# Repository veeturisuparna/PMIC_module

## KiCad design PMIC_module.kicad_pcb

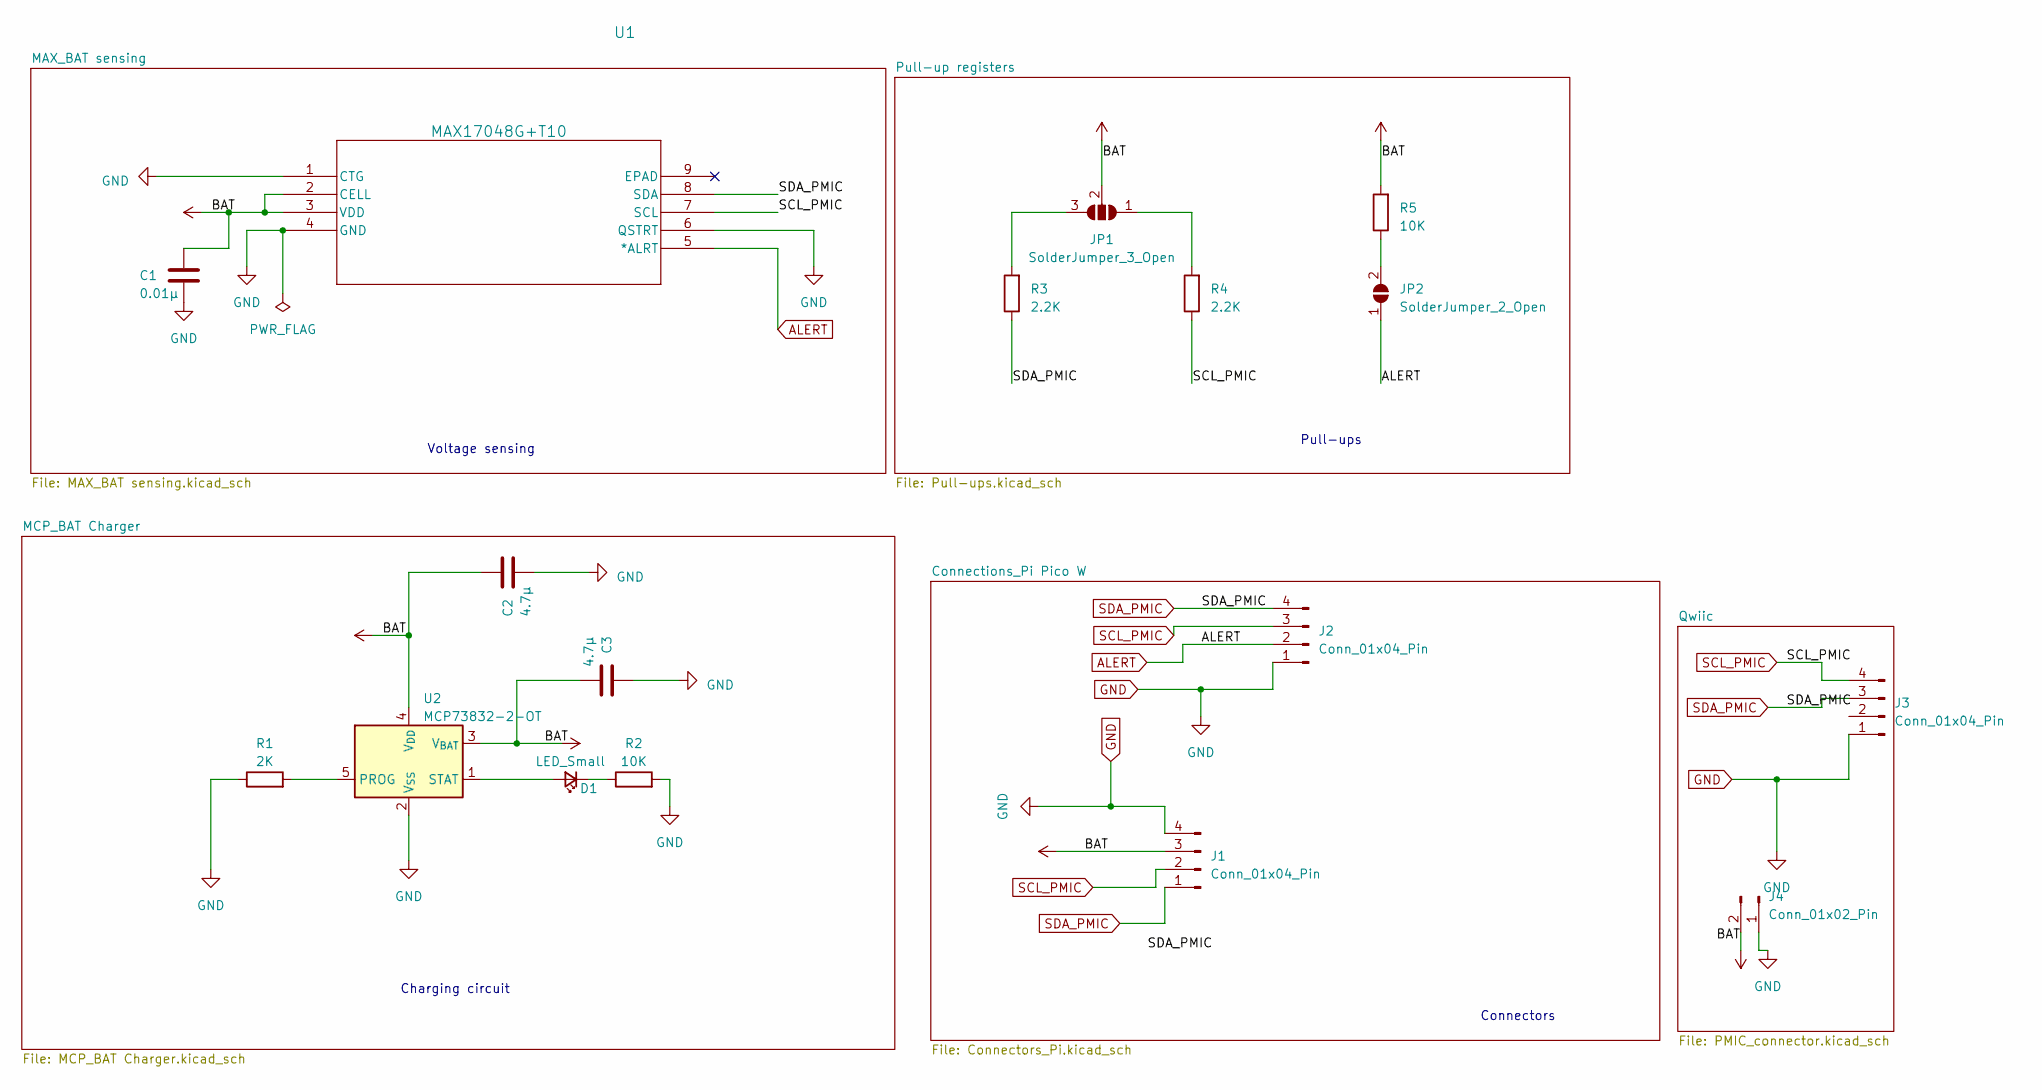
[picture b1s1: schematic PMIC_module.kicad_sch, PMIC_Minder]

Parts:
C1: 0.01µ; R_0603_1608Metric_Pad0.98x0.95mm_HandSolder
C2, C3: 4.7µ; R_0603_1608Metric_Pad0.98x0.95mm_HandSolder
D1: LED_Small; LED_0603_1608Metric_Pad1.05x0.95mm_HandSolder
J1, J2: Conn_01x04_Pin; Castellated_PinHeader_1x04_P2.54mm
J3: Conn_01x04_Pin; JST_PH_B4B-PH-SM4-TB_1x04-1MP_P2.00mm_Vertical
J4: Conn_01x02_Pin; JST_PH_S2B-PH-SM4-TB_1x02-1MP_P2.00mm_Horizontal
JP1: SolderJumper_3_Open; SolderJumper-3_P1.3mm_Open_Pad1.0x1.5mm
JP2: SolderJumper_2_Open; SolderJumper-2_P1.3mm_Open_Pad1.0x1.5mm
R1: 2K; R_0603_1608Metric_Pad0.98x0.95mm_HandSolder
R2, R5: 10K; R_0603_1608Metric_Pad0.98x0.95mm_HandSolder
R3, R4: 2.2K; R_0603_1608Metric_Pad0.98x0.95mm_HandSolder
U1: MAX17048G+T10; TDFN-8-1EP_2x2mm_P0.5mm_EP0.8x1.2mm
U2: MCP73832-2-OT; SOT-23-5

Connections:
+BATT: C1.1, C2.1, C3.2, J1.3, J4.2, JP1.2 (C), R5.2, U1.2 (CELL), U1.3 (VDD), U2.3 (V_{BAT}), U2.4 (V_{DD})
ALERT: J2.2, JP2.1 (A), U1.5 (*ALRT)
GND: C1.2, C2.2, C3.1, J1.4, J2.1, J3.1, J4.1, R1.1, R2.2, U1.1 (CTG), U1.4 (GND), U1.6 (QSTRT), U2.2 (V_{SS})
unnamed: D1.2 (A), U2.1 (STAT)
unnamed: D1.1 (K), R2.1
unnamed: JP1.1 (A), R4.2
unnamed: JP1.3 (B), R3.2
unnamed: JP2.2 (B), R5.1
unnamed: R1.2, U2.5 (PROG)
SCL_PMIC: J1.2, J2.3, J3.4, R4.1, U1.7 (SCL)
SDA_PMIC: J1.1, J2.4, J3.3, R3.1, U1.8 (SDA)

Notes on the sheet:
Voltage sensing
Connectors
Pull-ups
Charging circuit

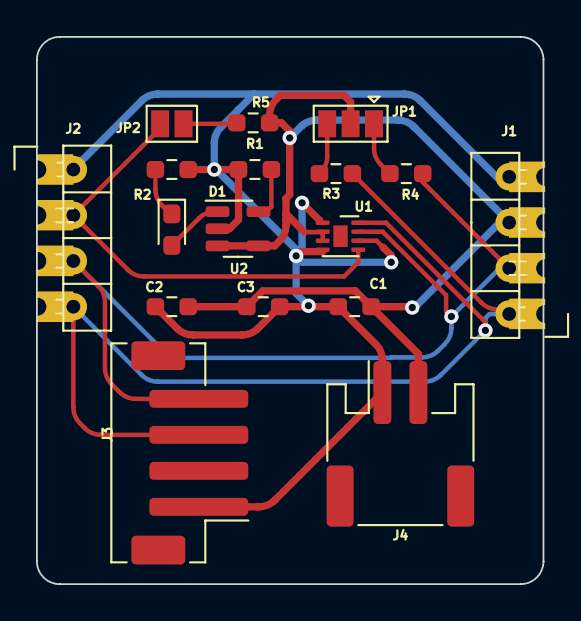
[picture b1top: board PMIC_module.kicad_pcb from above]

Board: 2 copper layers, 28.1 x 30.4 mm, 17 parts (0 on the bottom side), 11 nets.

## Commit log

2023-09-22 PMIC Gbr
